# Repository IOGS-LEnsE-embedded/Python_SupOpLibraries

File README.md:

# Python_SupOpLibraries
Librairies for Python interfacing projects developed by Institut d'Optique Graduate School / France

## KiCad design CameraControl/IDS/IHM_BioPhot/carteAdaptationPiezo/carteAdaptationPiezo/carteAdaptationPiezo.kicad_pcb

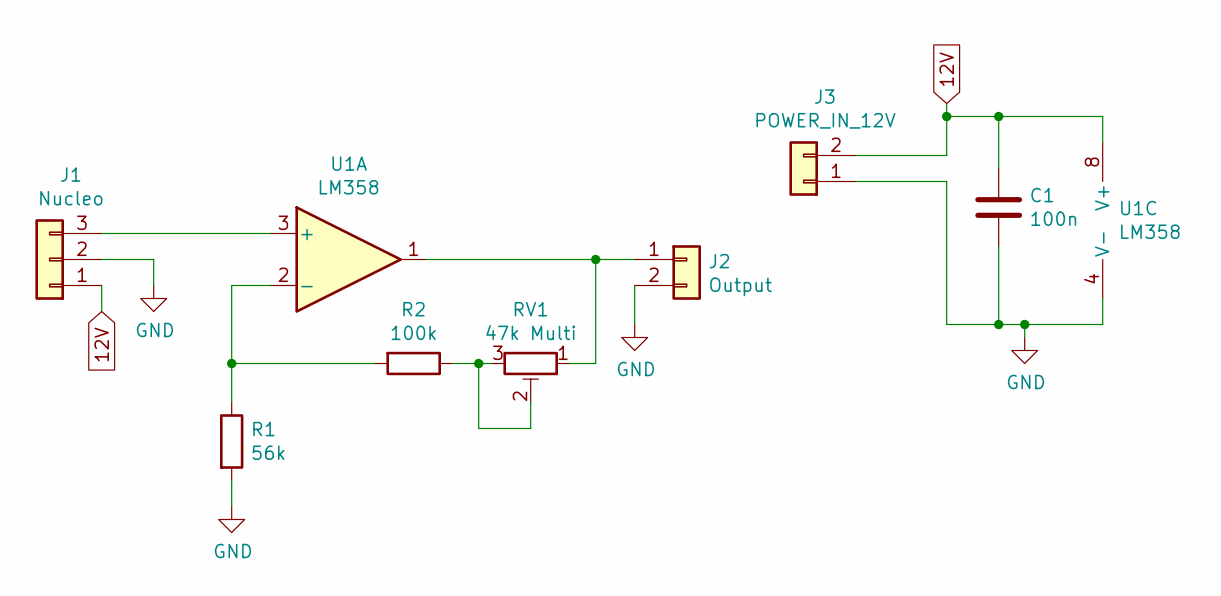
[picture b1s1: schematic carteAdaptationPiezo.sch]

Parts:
C1: 100n; C_Disc_D7.5mm_W5.0mm_P7.50mm
J1: Nucleo; PinHeader_1x03_P2.54mm_Horizontal
J2: Output; PinHeader_1x02_P2.54mm_Horizontal
J3: POWER_IN_12V; TerminalBlock_bornier-2_P5.08mm
R1: 56k; R_Axial_DIN0309_L9.0mm_D3.2mm_P12.70mm_Horizontal
R2: 100k; R_Axial_DIN0309_L9.0mm_D3.2mm_P12.70mm_Horizontal
RV1: 47k Multi; Potentiometer_Bourns_3296W_Vertical
U1: LM358; DIP-8_W7.62mm_LongPads

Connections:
12V: C1.1, J1.1, J3.2, U1.8 (V+)
GND: C1.2, J1.2, J2.2, J3.1, R1.2, U1.4 (V-)
unnamed: J1.3, U1.3 (+)
unnamed: J2.1, RV1.1, U1.1
unnamed: R1.1, R2.2, U1.2 (-)
unnamed: R2.1, RV1.2, RV1.3

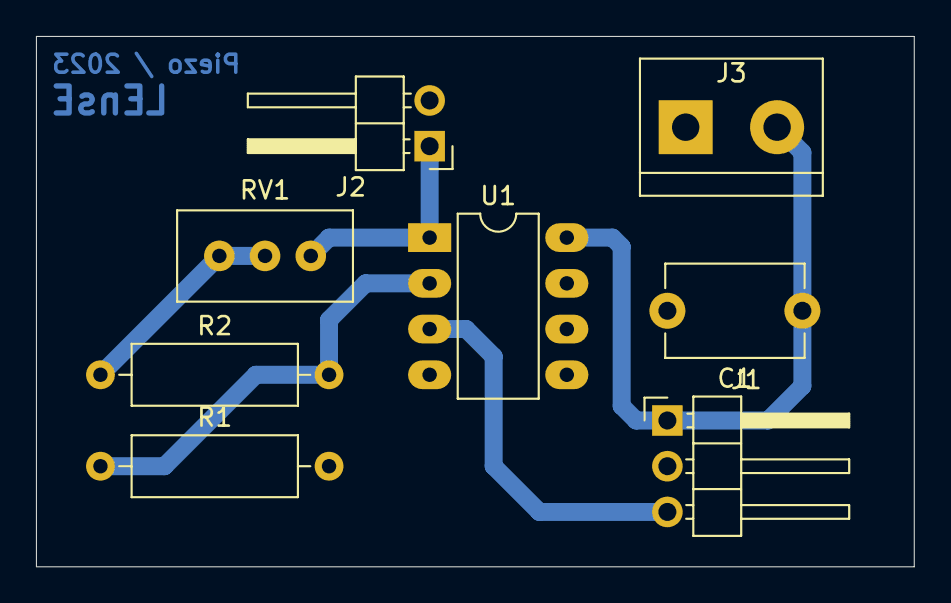
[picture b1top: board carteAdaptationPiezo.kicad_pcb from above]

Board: 2 copper layers, 48.8 x 29.5 mm, 8 parts (0 on the bottom side), 6 nets.

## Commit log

2023-04-18 Adding IDS Camera Python library and examples
2023-04-20 Adding PythonToNucleo communication examples (from jvillemejane)
2023-04-20 Updating PythonToNucleo GUI
2023-04-20 Updating PythonToNucleo example / cpp prog
2023-06-26 Adding version1 GUI for BioPhot Labwork
2023-06-29 Update BioDMD
2023-06-29 Update BioPhot
2023-06-30 Move BioPhot and CMOS Sensor from CameraControl
